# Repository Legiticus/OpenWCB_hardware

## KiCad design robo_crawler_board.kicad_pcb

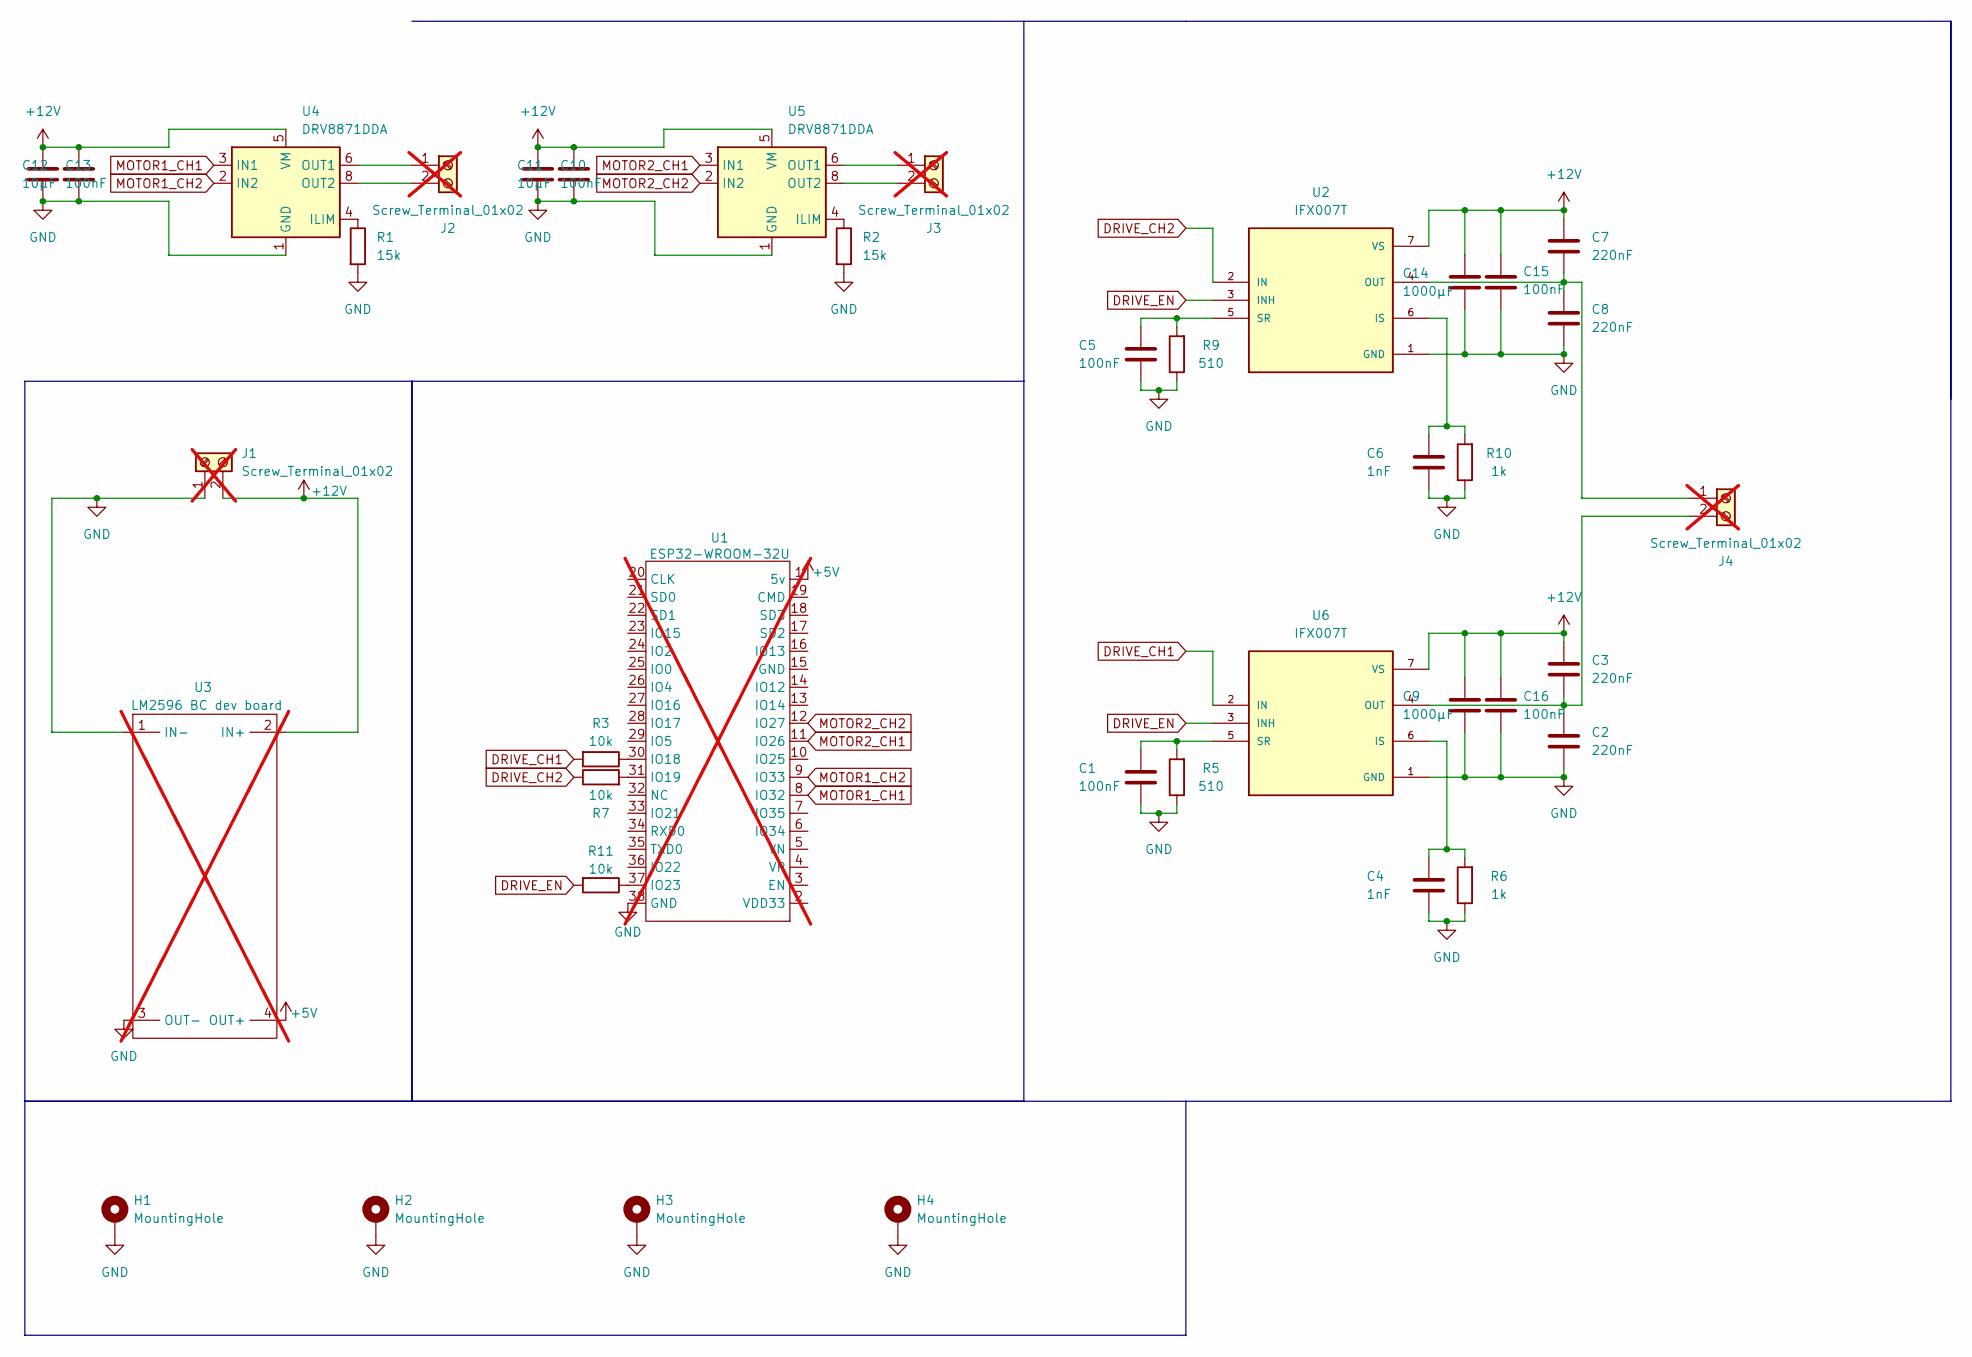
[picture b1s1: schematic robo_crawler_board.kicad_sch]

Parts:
C1, C5, C10, C13, C15, C16: 100nF; C_0805_2012Metric; LCSC Part Number C49678
C2, C3, C7, C8: 220nF; C_0805_2012Metric; LCSC Part Number C513710
C4, C6: 1nF; C_0805_2012Metric; LCSC Part Number C51210
C9, C14: 1000µF; CP_Radial_D10.0mm_P5.00mm; LCSC Part Number C233098
C11, C12: 10µF; C_0805_2012Metric; LCSC Part Number C83170
H1, H2, H3, H4: MountingHole; MountingHole_2.2mm_M2_Pad
J1, J2, J3, J4: Screw_Terminal_01x02; TerminalBlock_bornier-2_P5.08mm; not fitted
R1, R2: 15k; R_0805_2012Metric; LCSC Part Number C17475
R3, R7, R11: 10k; R_0805_2012Metric; LCSC Part Number C17414
R5, R9: 510; R_0805_2012Metric; LCSC Part Number C2907333
R6, R10: 1k; R_0805_2012Metric; LCSC Part Number C17513
U1: esp32-32u; Manufacturer Part ESP32-WROOM-32U; LCSC Part Name ESP32-WROOM-32U; not fitted
U2, U6: IFX007T; TO127P1500X440-8N; PARTREV 1.0; LCSC Part Number C6968485
U3: LM2596 DC-DC Buck Converter; not fitted
U4, U5: DRV8871DDA; Texas_HTSOP-8-1EP_3.9x4.9mm_P1.27mm_EP2.95x4.9mm_Mask2.4x3.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; LCSC Part Number C1556867

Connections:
+5V: U1.1 (5v), U3.4 (OUT+)
+12V: C3.1, C7.1, C9.1, C10.1, C11.1, C12.1, C13.1, C14.1, C15.1, C16.1, J1.2, U2.7 (VS), U3.2 (IN+), U4.5 (VM), U5.5 (VM), U6.7 (VS)
DRIVE_CH1: R3.2, U6.2 (IN)
DRIVE_CH2: R7.1, U2.2 (IN)
DRIVE_EN: R11.2, U2.3 (INH), U6.3 (INH)
GND: C1.2, C2.2, C4.2, C5.2, C6.2, C8.2, C9.2, C10.2, C11.2, C12.2, C13.2, C14.2, C15.2, C16.2, H1.1, H2.1, H3.1, H4.1, J1.1, R1.2, R2.2, R5.1, R6.1, R9.1, R10.1, U1.38 (GND), U2.1 (GND), U3.1 (IN-), U3.3 (OUT-), U4.1 (GND), U4.7 (GND), U4.9 (GND), U5.1 (GND), U5.7 (GND), U5.9 (GND), U6.1 (GND)
MOTOR1_CH1: U1.8 (IO32), U4.3 (IN1)
MOTOR1_CH2: U1.9 (IO33), U4.2 (IN2)
MOTOR2_CH1: U1.11 (IO26), U5.3 (IN1)
MOTOR2_CH2: U1.12 (IO27), U5.2 (IN2)
unnamed: J2.1, U4.6 (OUT1)
unnamed: J2.2, U4.8 (OUT2)
unnamed: J3.1, U5.6 (OUT1)
unnamed: J3.2, U5.8 (OUT2)
unnamed: C7.2, C8.1, J4.1, U2.4 (OUT), U2.8 (OUT)
unnamed: C2.1, C3.2, J4.2, U6.4 (OUT), U6.8 (OUT)
unnamed: R3.1, U1.30 (IO18)
unnamed: R7.2, U1.31 (IO19)
unnamed: R11.1, U1.37 (IO23)
unnamed: C6.1, R10.2, U2.6 (IS)
unnamed: C5.1, R9.2, U2.5 (SR)
unnamed: R1.1, U4.4 (ILIM)
unnamed: R2.1, U5.4 (ILIM)
unnamed: C4.1, R6.2, U6.6 (IS)
unnamed: C1.1, R5.2, U6.5 (SR)

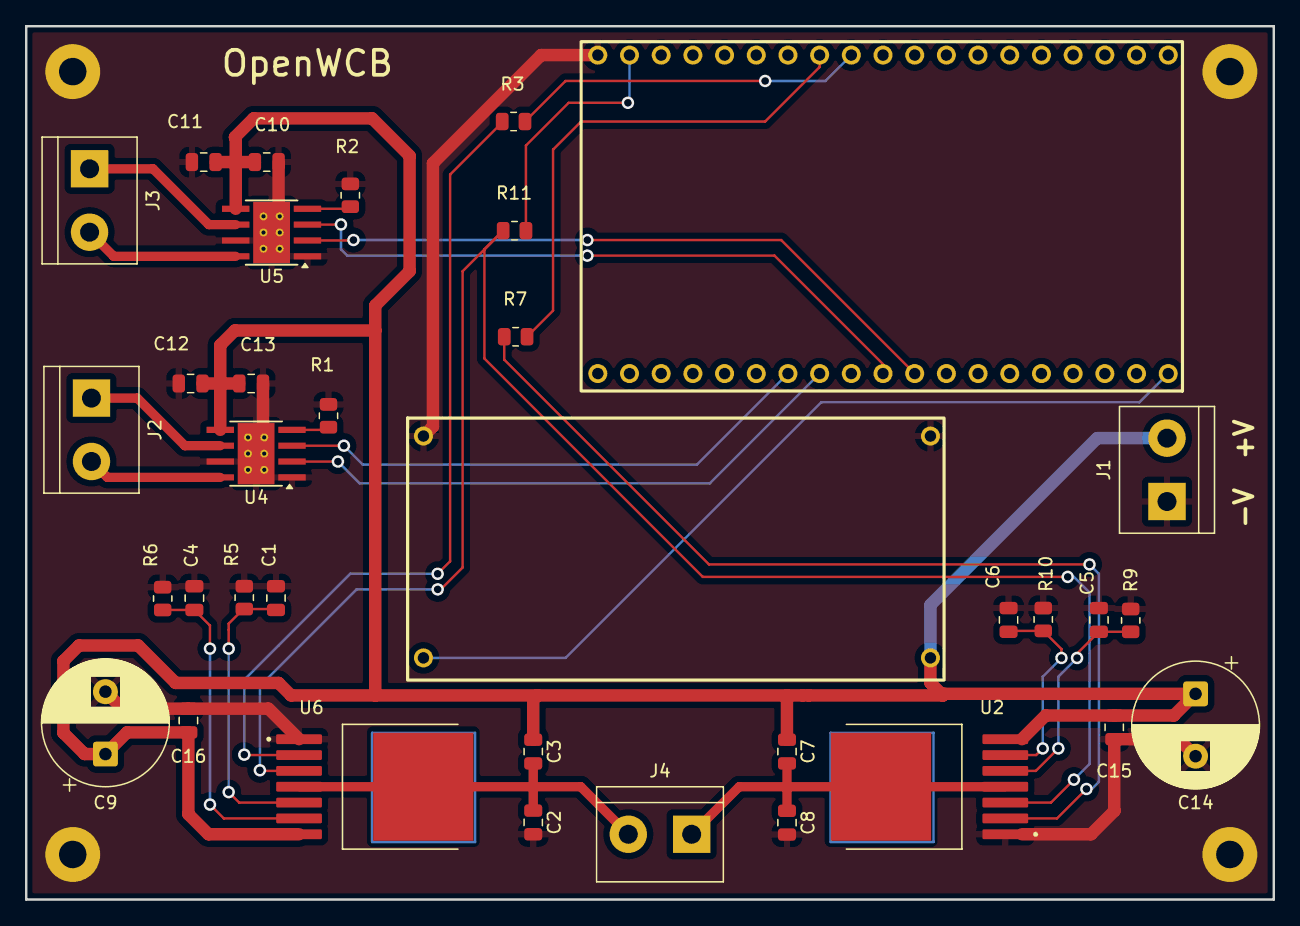
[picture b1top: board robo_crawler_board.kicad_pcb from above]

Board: 2 copper layers, 100.0 x 70.0 mm, 39 parts (0 on the bottom side), 25 nets.

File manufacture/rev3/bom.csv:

Designator,Footprint,Quantity,Value,LCSC Part #
"C1, C10, C13, C15, C16, C5",0805,6,100nF,C49678
"C11, C12",0805,2,10µF,C83170
"C14, C9",CP_Radial_D10.0mm_P5.00mm,2,1000µF,C233098
"C2, C3, C7, C8",0805,4,220nF,C513710
"C4, C6",0805,2,1nF,C51210
"R1, R2",0805,2,15k,C17475
"R10, R6",0805,2,1k,C17513
"R11, R3, R7",0805,3,10k,C17414
"R5, R9",0805,2,510,C2907333
"U2, U6",TO127P1500X440-8N,2,IFX007T,C6968485
"U4, U5",Texas_HTSOP-8-1EP_3.9x4.9mm_P1.27mm_EP2.95x4.9mm_Mask2.4x3.1mm_ThermalVias,2,DRV8871DDA,C1556867

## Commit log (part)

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2026-02-23 adjusted for EPL manufacturing
2026-03-26 cleaning repo
2026-03-26 created README.md
2026-03-26 Create LICENSE
2026-03-26 Reworking board design
2026-03-26 tentative rev2
2026-03-30 rev 2
2026-05-18 removed unnessesary controllers and adjusted layout
2026-05-18 saving progress
2026-06-16 updating
